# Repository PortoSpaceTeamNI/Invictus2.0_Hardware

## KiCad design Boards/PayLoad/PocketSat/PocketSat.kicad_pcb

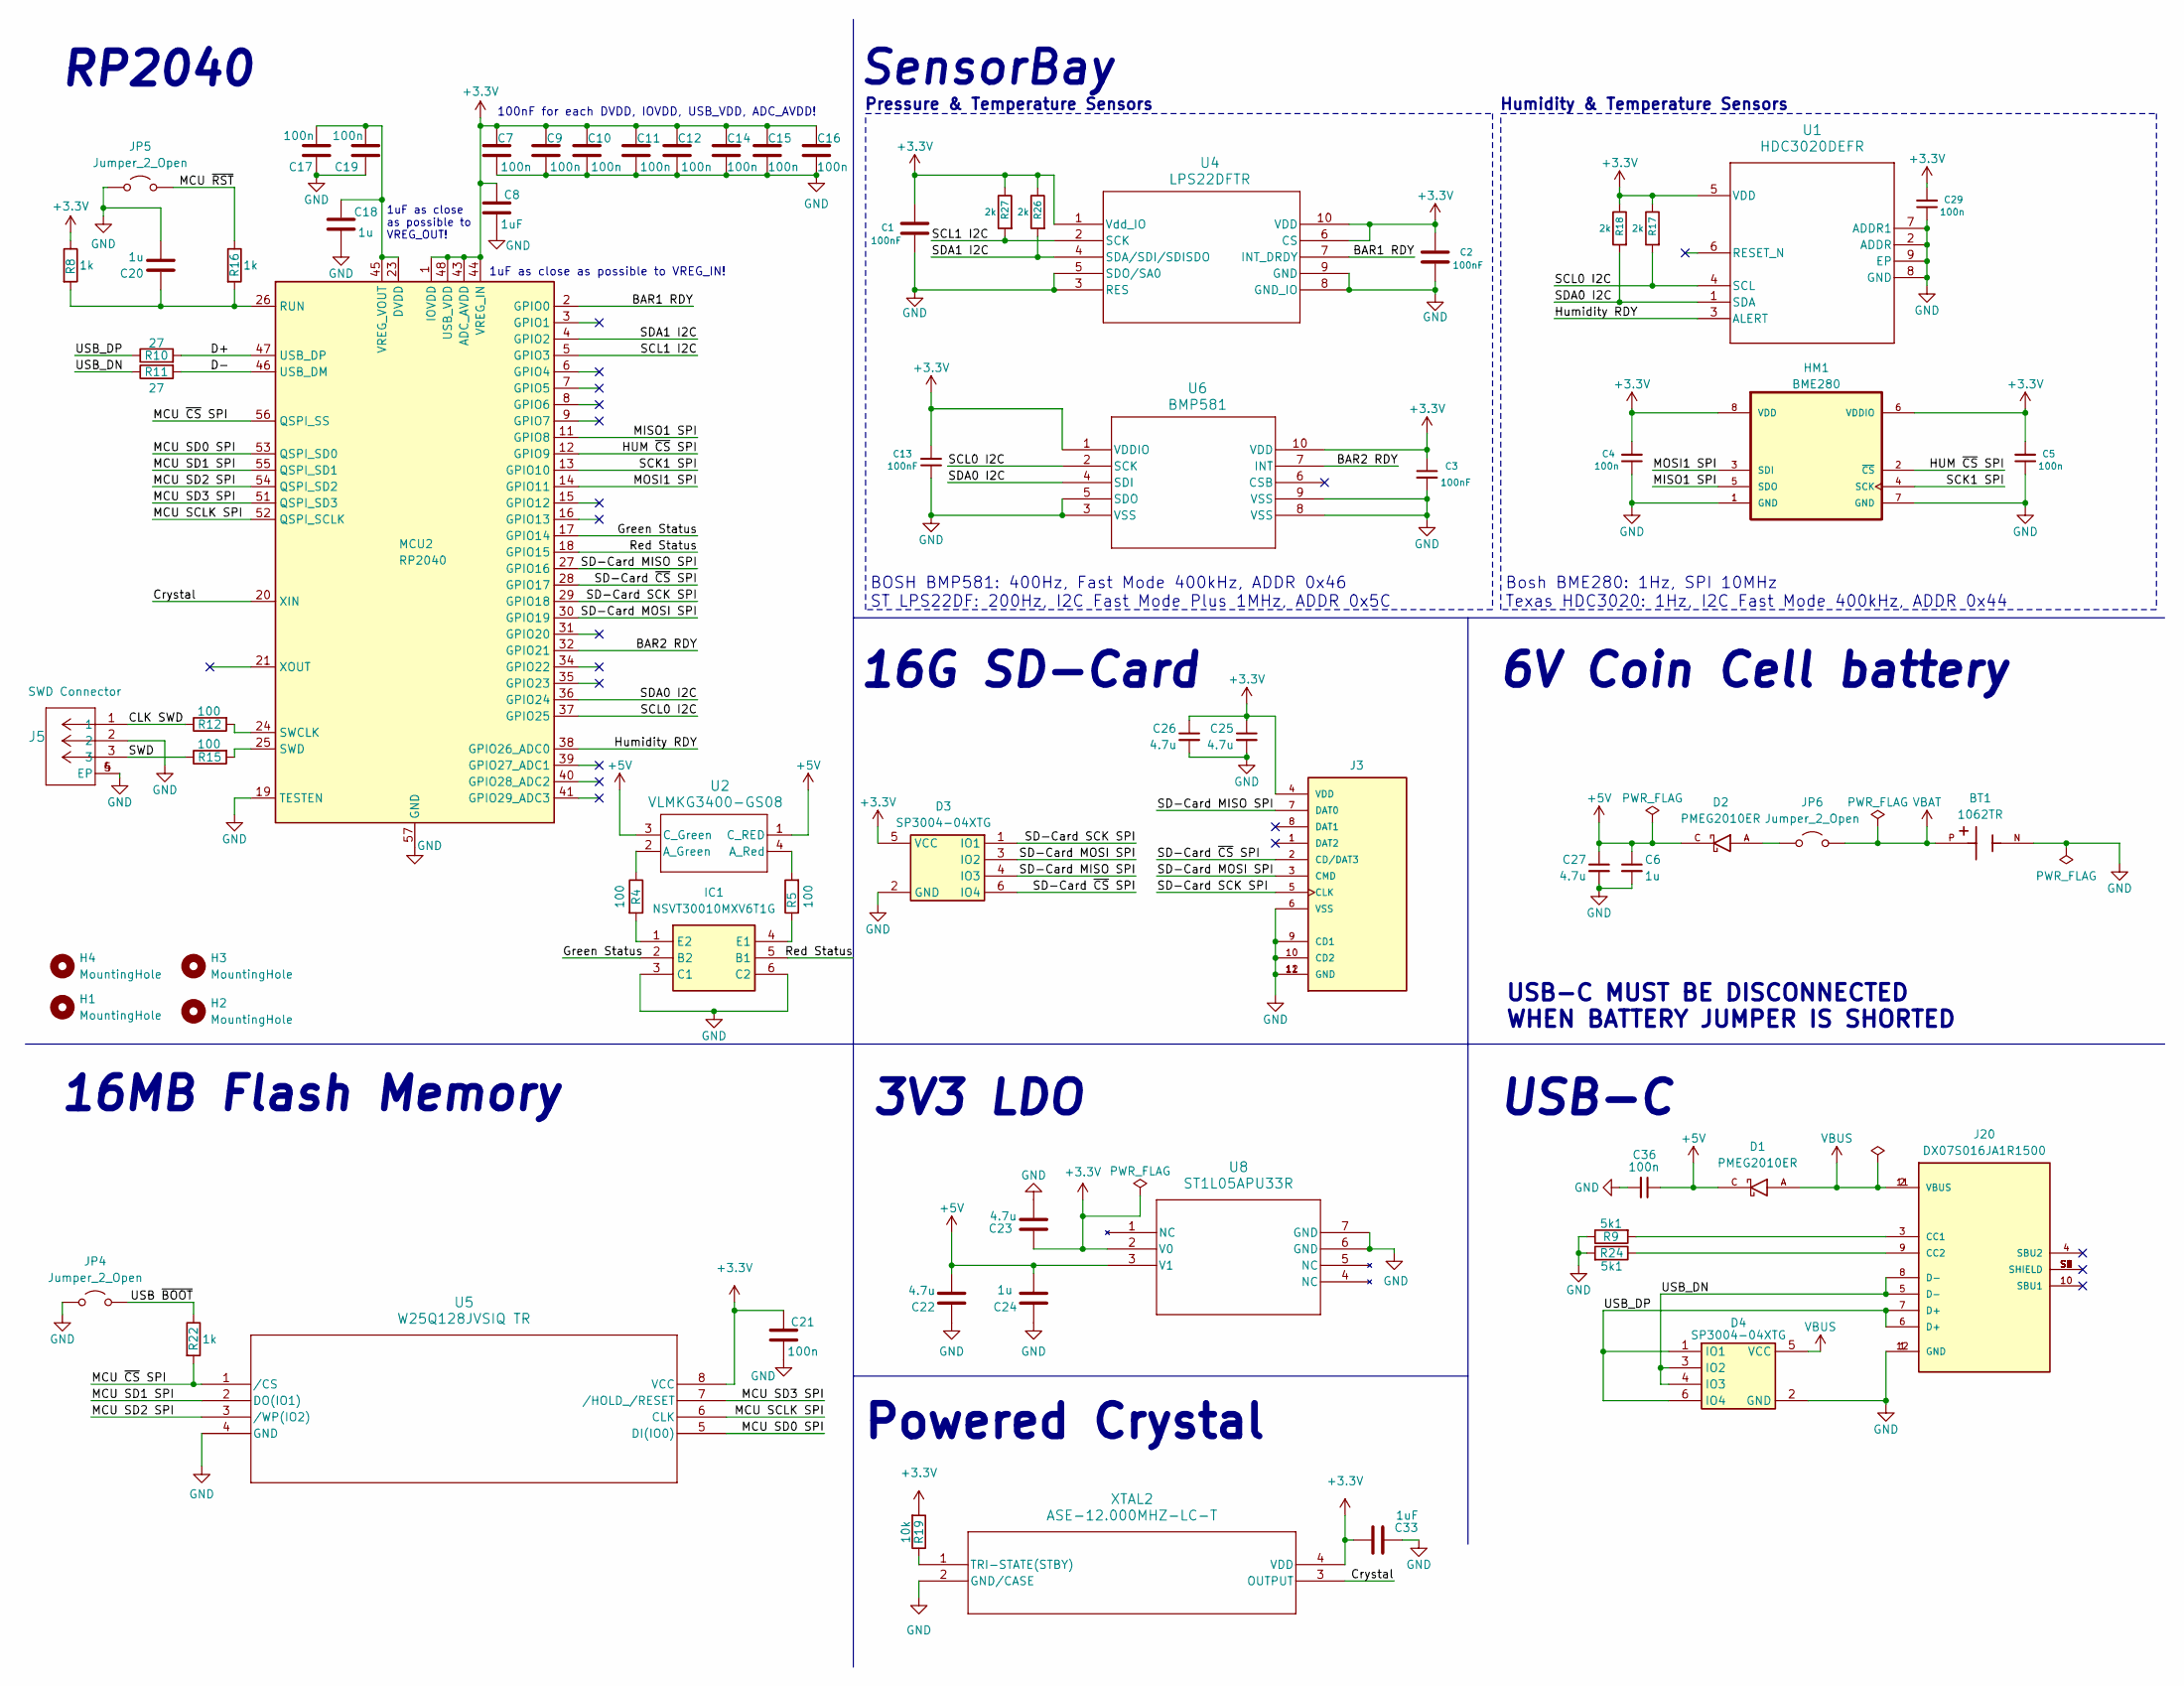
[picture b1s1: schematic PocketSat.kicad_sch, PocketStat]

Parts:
BT1: 1062TR; BAT_1062TR; PARTREV F
C1, C2, C3, C13: 100nF; Capacitor_0402
C4, C5, C7, C9, C10, C11, C12, C14, C15, C16, C17, C19, C21, C29, C36: 100n; Capacitor_0402
C6, C18, C20, C24: 1u; Capacitor_0402
C8, C33: 1uF; Capacitor_0402
C22, C23, C25, C26, C27: 4.7u; Capacitor_0402
D1, D2: PMEG2010ER; SODFL3517X110N; PARTREV 01
D3, D4: SP3004-04XTG; SOT563_LTF; Mouser Part Number 576-SP3004-04XTG
H1, H2, H3, H4: MountingHole; MountingHole_2.2mm_M2_ISO7380
HM1: BME280; Mouser Part Number 262-BME280
IC1: NSVT30010MXV6T1G; SOT-563_1P3X1P7_ONS; Mouser Part Number 863-NSVT30010MXV6T1G
J3: MEM2061-01-188-00-A_REVA; GCT_MEM2061-01-188-00-A_REVA
J5: BM03B-SRSS-TBLFSN; CONN_BM03B-SRSS-TBLFSN_JST
J20: DX07S016JA1R1500; JAE_DX07S016JA1R1500; PARTREV 1
JP4, JP5, JP6: Jumper_2_Open; SolderJumper-2_P1.3mm_Open_RoundedPad1.0x1.5mm
MCU2: RP2040; QFN56_7X7_RPI
R4, R5: 100; RES_0603
R8, R16, R22: 1k; RES_0402
R9, R24: 5k1; RES_0402
R10, R11: 27; RES_0402
R12, R15: 100; RES_0402
R17, R18, R26, R27: 2k; RES_0402
R19: 10k; RES_0402
U1: HDC3020DEFR; DEF0008A-IPC_C
U2: VLMKG3400-GS08; SMT_00-GS08_VIS
U4: LPS22DFTR; QFN_22DFTR_STM
U5: W25Q128JVSIQ TR; SOIC_208MIL_WIN
U6: BMP581; QFN10_BMP581_BOS
U8: ST1L05APU33R; DFN_5APU33R_STM
XTAL2: ASE-12.000MHZ-LC-T; ASE24576MHZLCT

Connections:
+3.3V: C1.2, C2.2, C3.1, C4.2, C5.2, C7.1, C8.1, C9.1, C10.1, C11.1, C12.1, C13.2, C14.1, C15.1, C16.1, C21.1, C23.2, C25.1, C26.1, C29.2, C33.1, D3.5 (VCC), HM1.6 (VDDIO), HM1.8 (VDD), J3.4 (VDD), MCU2.1 (IOVDD), MCU2.10 (IOVDD), MCU2.22 (IOVDD), MCU2.33 (IOVDD), MCU2.42 (IOVDD), MCU2.43 (ADC_AVDD), MCU2.44 (VREG_IN), MCU2.48 (USB_VDD), MCU2.49 (IOVDD), R8.1, R17.1, R18.1, R19.2, R26.1, R27.1, U1.5 (VDD), U4.1 (Vdd_IO), U4.6 (CS), U4.10 (VDD), U5.8 (VCC), U6.1 (VDDIO), U6.10 (VDD), U8.2 (V0), XTAL2.4 (VDD)
+5V: C6.1, C22.2, C24.2, C27.1, C36.1, D1.C, D2.C, U2.1 (C_RED), U2.3 (C_Green), U8.3 (V1)
/BAR1 RDY: MCU2.2 (GPIO0), U4.7 (INT_DRDY)
/BAR2 RDY: MCU2.32 (GPIO21), U6.7 (INT)
/CLK SWD: J5.1, R12.1
/Crystal: MCU2.20 (XIN), XTAL2.3 (OUTPUT)
/D+: MCU2.47 (USB_DP), R10.2
/D-: MCU2.46 (USB_DM), R11.2
/Green Status: IC1.2 (B2), MCU2.17 (GPIO14)
/HUM ~CS SPI: HM1.2 (~CS), MCU2.12 (GPIO9)
/Humidity RDY: MCU2.38 (GPIO26_ADC0), U1.3 (ALERT)
/MCU SCLK SPI: MCU2.52 (QSPI_SCLK), U5.6 (CLK)
/MCU SD0 SPI: MCU2.53 (QSPI_SD0), U5.5 (DI(IO0))
/MCU SD1 SPI: MCU2.55 (QSPI_SD1), U5.2 (DO(IO1))
/MCU SD2 SPI: MCU2.54 (QSPI_SD2), U5.3 (/WP(IO2))
/MCU SD3 SPI: MCU2.51 (QSPI_SD3), U5.7 (/HOLD_/RESET)
/MCU ~CS SPI: MCU2.56 (QSPI_SS), R22.2, U5.1 (/CS)
/MCU ~RST: JP5.2 (B), R16.1
/MISO1 SPI: HM1.5 (SDO), MCU2.11 (GPIO8)
/MOSI1 SPI: HM1.3 (SDI), MCU2.14 (GPIO11)
/Red Status: IC1.5 (B1), MCU2.18 (GPIO15)
/SCK1 SPI: HM1.4 (SCK), MCU2.13 (GPIO10)
/SCL0 I2C: MCU2.37 (GPIO25), R17.2, U1.4 (SCL), U6.2 (SCK)
/SCL1 I2C: MCU2.5 (GPIO3), R27.2, U4.2 (SCK)
/SD-Card ~CS SPI: D3.6 (IO4), J3.2 (CD/DAT3), MCU2.28 (GPIO17)
/SD-Card MISO SPI: D3.4 (IO3), J3.7 (DAT0), MCU2.27 (GPIO16)
/SD-Card MOSI SPI: D3.3 (IO2), J3.3 (CMD), MCU2.30 (GPIO19)
/SD-Card SCK SPI: D3.1 (IO1), J3.5 (CLK), MCU2.29 (GPIO18)
/SDA0 I2C: MCU2.36 (GPIO24), R18.2, U1.1 (SDA), U6.4 (SDI)
/SDA1 I2C: MCU2.4 (GPIO2), R26.2, U4.4 (SDA/SDI/SDISDO)
/SWD: J5.3, R15.1
/USB ~BOOT: JP4.2 (B), R22.1
/USB_DN: D4.3 (IO2), D4.4 (IO3), J20.5 (D-), J20.8 (D-), R11.1
/USB_DP: D4.1 (IO1), D4.6 (IO4), J20.6 (D+), J20.7 (D+), R10.1
GND: BT1.N, C1.1, C2.1, C3.2, C4.1, C5.1, C6.2, C7.2, C8.2, C9.2, C10.2, C11.2, C12.2, C13.1, C14.2, C15.2, C16.2, C17.1, C18.2, C19.1, C20.2, C21.2, C22.1, C23.1, C24.1, C25.2, C26.2, C27.2, C29.1, C33.2, C36.2, D3.2 (GND), D4.2 (GND), HM1.1 (GND), HM1.7 (GND), IC1.3 (C1), IC1.6 (C2), J3.6 (VSS), J3.9 (CD1), J3.10 (CD2), J3.11 (GND), J3.12 (GND), J5.2, J5.4 (EP), J5.5 (EP), J20.1 (GND), J20.12 (GND), JP4.1 (A), JP5.1 (A), MCU2.19 (TESTEN), MCU2.57 (GND), R9.1, R24.2, U1.2 (ADDR), U1.7 (ADDR1), U1.8 (GND), U1.9 (EP), U4.3 (RES), U4.5 (SDO/SA0), U4.8 (GND_IO), U4.9 (GND), U5.4 (GND), U6.3 (VSS), U6.5 (SDO), U6.8 (VSS), U6.9 (VSS), U8.6 (GND), U8.7 (GND), XTAL2.2 (GND/CASE)
unnamed: IC1.4 (E1), R5.1
unnamed: IC1.1 (E2), R4.2
unnamed: J20.3 (CC1), R9.2
unnamed: J20.9 (CC2), R24.1
unnamed: D2.A, JP6.1 (A)
unnamed: C20.1, MCU2.26 (RUN), R8.2, R16.2
unnamed: MCU2.24 (SWCLK), R12.2
unnamed: MCU2.25 (SWD), R15.2
unnamed: C17.2, C18.1, C19.2, MCU2.23 (DVDD), MCU2.45 (VREG_VOUT), MCU2.50 (DVDD)
unnamed: R4.1, U2.2 (A_Green)
unnamed: R5.2, U2.4 (A_Red)
unnamed: R19.1, XTAL2.1 (TRI-STATE(STBY))
VBAT: BT1.P, JP6.2 (B)
VBUS: D1.A, D4.5 (VCC), J20.2 (VBUS), J20.11 (VBUS)

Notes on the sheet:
BOSH BMP581: 400Hz, Fast Mode 400kHz, ADDR 0x46 ST LPS22DF: 200Hz, I2C Fast Mode Plus 1MHz, ADDR 0x5C
SensorBay
100nF for each DVDD, IOVDD, USB_VDD, ADC_AVDD!
3V3 LDO
RP2040
USB-C
Powered Crystal
Humidity & Temperature Sensors
16G SD-Card
6V Coin Cell battery
Pressure & Temperature Sensors
16MB Flash Memory
Bosh BME280: 1Hz, SPI 10MHz Texas HDC3020: 1Hz, I2C Fast Mode 400kHz, ADDR 0x44
1uF as close as possible to VREG_OUT!
1uF as close as possible to VREG_IN!
USB-C MUST BE DISCONNECTED WHEN BATTERY JUMPER IS SHORTED

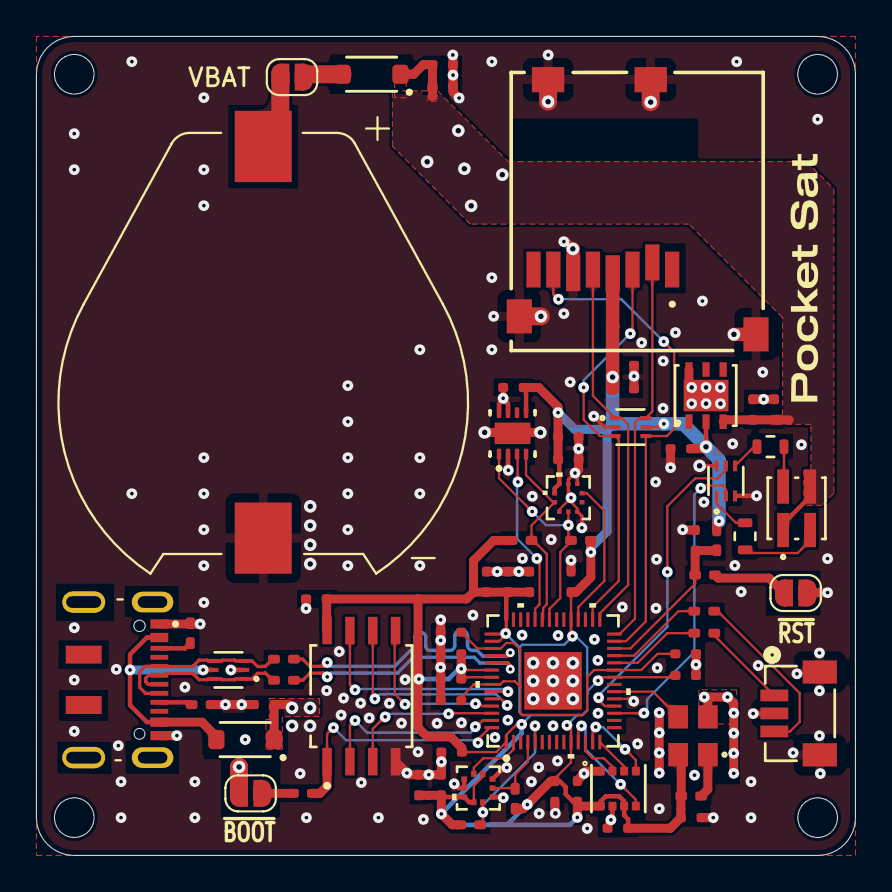
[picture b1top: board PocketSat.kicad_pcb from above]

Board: 4 copper layers, 45.5 x 45.5 mm, 71 parts (0 on the bottom side), 49 nets.

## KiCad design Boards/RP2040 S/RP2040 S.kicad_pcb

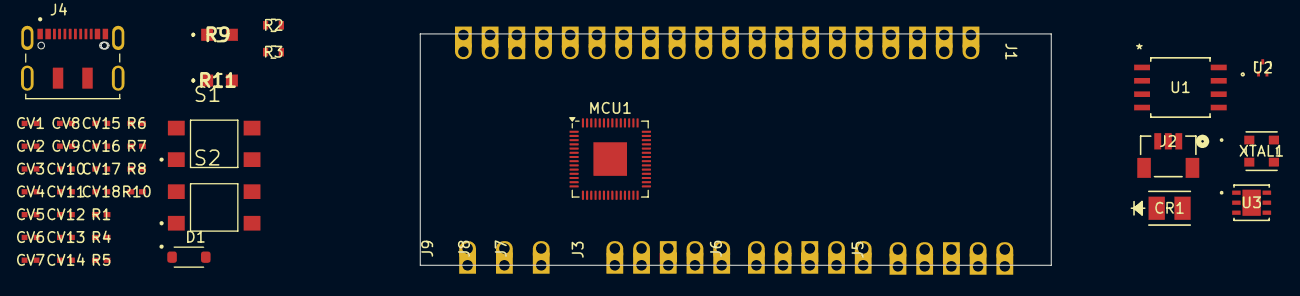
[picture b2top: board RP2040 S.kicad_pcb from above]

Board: 4 copper layers, 47 parts (0 on the bottom side), 57 nets, no tracks yet.

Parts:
CR1: VLMC3100-GS08; LED_PLCC_VSMB
CV1, CV3, CV6, CV13, CV17: 1uF; Capacitor_0402
CV2, CV4, CV5, CV7, CV8, CV9, CV10, CV11, CV12, CV14, CV18: 100nF; Capacitor_0402
CV15, CV16: 4.7uF; Capacitor_0402
D1: PMEG2010ER; SODFL3517X110N
J1: Conn_01x20_Socket; Pico_20pin
J2: BM03B-SRSS-TBLFSN; CONN_BM03B-SRSS-TBLFSN_JST
J3, J5, J6: Conn_01x05_Socket; Pico_05pin
J4: DX07S016JA1R1500; JAE_DX07S016JA1R1500
J7, J8, J9: Conn_01x01_Socket; Pico_01pin
MCU1: RP2040; QFN-56-1EP_7x7mm_P0.4mm_EP3.2x3.2mm
R1, R6, R10: 1k; RES_0402
R2, R3: 27; RES_0603
R4, R5: 100; RES_0402
R7: 10k; RES_0402
R8: 665; RES_0402
R9, R11: 5k1; RES_0805
S1, S2: TL3305CF160QG; SW_TL3305CF160QG
U1: W25Q128JVSIQ TR; SOIC_208MIL_WIN
U2: ESD7L5.0DT5G; SOT-723_0P85X1P25_ONS
U3: ST1L05APU33R; DFN_5APU33R_STM
XTAL1: ASE-12.000MHZ-LC-T; ASE-3.2X2.5_ABR

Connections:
+3.3V: CV5.1, CV6.1, CV7.1, CV8.1, CV9.1, CV10.1, CV11.1, CV12.1, CV13.1, CV14.1, CV16.2, CV18.1, MCU1.1 (IOVDD), MCU1.10 (IOVDD), MCU1.22 (IOVDD), MCU1.33 (IOVDD), MCU1.42 (IOVDD), MCU1.43 (ADC_AVDD), MCU1.44 (VREG_IN), MCU1.48 (USB_VDD), MCU1.49 (IOVDD), R1.1, R7.2, U1.8 (VCC), U3.2 (V0), XTAL1.4 (VDD)
/RP2040 Standard/+5V: CV15.2, CV17.2, D1.C, J3.1, U3.3 (V1)
/RP2040 Standard/GP0/UART0 TX: J1.20, MCU1.2 (GPIO0)
/RP2040 Standard/GP1/UART0 RX: J1.19, MCU1.3 (GPIO1)
/RP2040 Standard/GP2/UART0 CTS: J1.18, MCU1.4 (GPIO2)
/RP2040 Standard/GP3/UART0 RTS: J1.17, MCU1.5 (GPIO3)
/RP2040 Standard/GP4/UART1 TX: J1.15, MCU1.6 (GPIO4)
/RP2040 Standard/GP5/UART1 RX: J1.14, MCU1.7 (GPIO5)
/RP2040 Standard/GP6/UART1 CTS: J1.13, MCU1.8 (GPIO6)
/RP2040 Standard/GP7/UART1 RTS: J1.12, MCU1.9 (GPIO7)
/RP2040 Standard/GP8/SPI1 MISO: J1.10, MCU1.11 (GPIO8)
/RP2040 Standard/GP9/SPI1 ~CS: J1.9, MCU1.12 (GPIO9)
/RP2040 Standard/GP10/SPI1 SCK: J1.8, MCU1.13 (GPIO10)
/RP2040 Standard/GP11/SPI1 MOSI: J1.7, MCU1.14 (GPIO11)
/RP2040 Standard/GP12/I2C0 SDA: J1.5, MCU1.15 (GPIO12)
/RP2040 Standard/GP13/I2C0 SCL: J1.4, MCU1.16 (GPIO13)
/RP2040 Standard/GP14/I2C1 SDA: J1.2, MCU1.17 (GPIO14)
/RP2040 Standard/GP15/I2C1 SCL: J1.1, MCU1.18 (GPIO15)
/RP2040 Standard/GP16/SPI0 MISO: J3.2, MCU1.27 (GPIO16)
/RP2040 Standard/GP17/SPI0 ~CS: J3.3, MCU1.28 (GPIO17)
/RP2040 Standard/GP18/SPI0 SCK: J3.4, MCU1.29 (GPIO18)
/RP2040 Standard/GP19/SPI0 MOSI: J3.5, MCU1.30 (GPIO19)
/RP2040 Standard/GP20/PWM2 A/CLKIN 0: J5.2, MCU1.31 (GPIO20)
/RP2040 Standard/GP21/PWM2 B/CLKOUT 0: J5.3, MCU1.32 (GPIO21)
/RP2040 Standard/GP22/PWM3 A/CLKIN 1: J5.4, MCU1.34 (GPIO22)
/RP2040 Standard/GP23/PWM3 B/CLKOUT 1: J5.5, MCU1.35 (GPIO23)
/RP2040 Standard/GP24/PWM4 A: J6.2, MCU1.36 (GPIO24)
/RP2040 Standard/GP26_ADC0: J6.4, MCU1.38 (GPIO26_ADC0)
/RP2040 Standard/GP27_ADC1: J6.5, MCU1.39 (GPIO27_ADC1)
/RP2040 Standard/GP28_ADC2: J7.1, MCU1.40 (GPIO28_ADC2)
/RP2040 Standard/GP29_ADC3: J8.1, MCU1.41 (GPIO29_ADC3)
/RP2040 Standard/MCU QSPI_SCLK: MCU1.52 (QSPI_SCLK), U1.6 (CLK)
/RP2040 Standard/MCU QSPI_SD0: MCU1.53 (QSPI_SD0), U1.5 (DI(IO0))
/RP2040 Standard/MCU QSPI_SD1: MCU1.55 (QSPI_SD1), U1.2 (DO(IO1))
/RP2040 Standard/MCU QSPI_SD2: MCU1.54 (QSPI_SD2), U1.3 (/WP(IO2))
/RP2040 Standard/MCU QSPI_SD3: MCU1.51 (QSPI_SD3), U1.7 (/HOLD_/RESET)
/RP2040 Standard/MCU QSPI_SS: MCU1.56 (QSPI_SS), R10.2, U1.1 (/CS)
/RP2040 Standard/USB_DM: J4.5 (D-), J4.8 (D-), R3.1, U2.1
/RP2040 Standard/USB_DP: J4.6 (D+), J4.7 (D+), R2.1, U2.2
/RP2040 Standard/~RST: R6.1, S1.4
/RP2040 Standard/~USB_BOOT: R10.1, S2.4
CRYSTAL: MCU1.20 (XIN), XTAL1.3 (OUTPUT)
GND: CR1.1, CV1.2, CV2.1, CV3.2, CV4.1, CV5.2, CV6.2, CV7.2, CV8.2, CV9.2, CV10.2, CV11.2, CV12.2, CV13.2, CV14.2, CV15.1, CV16.1, CV17.1, CV18.2, J1.3, J1.6, J1.11, J1.16, J2.2, J4.1 (GND), J4.12 (GND), J5.1, J6.1, J6.3, J9.1, MCU1.19 (TESTEN), MCU1.57 (GND), R9.1, R11.1, S1.2, S2.2, U1.4 (GND), U2.3, U3.6 (GND), U3.7 (GND), XTAL1.2 (GND/CASE)
unnamed: CR1.2, R8.2
unnamed: D1.A, J4.2 (VBUS), J4.11 (VBUS)
unnamed: J2.1, R4.1
unnamed: J2.3, R5.1
unnamed: J4.3 (CC1), R11.2
unnamed: J4.9 (CC2), R9.2
unnamed: MCU1.37 (GPIO25), R8.1
unnamed: CV1.1, MCU1.26 (RUN), R1.2, R6.2
unnamed: MCU1.24 (SWCLK), R4.2
unnamed: MCU1.25 (SWD), R5.2
unnamed: MCU1.46 (USB_DM), R3.2
unnamed: MCU1.47 (USB_DP), R2.2
unnamed: CV2.2, CV3.1, CV4.2, MCU1.23 (DVDD), MCU1.45 (VREG_VOUT), MCU1.50 (DVDD)
unnamed: R7.1, XTAL1.1 (TRI-STATE(STBY))

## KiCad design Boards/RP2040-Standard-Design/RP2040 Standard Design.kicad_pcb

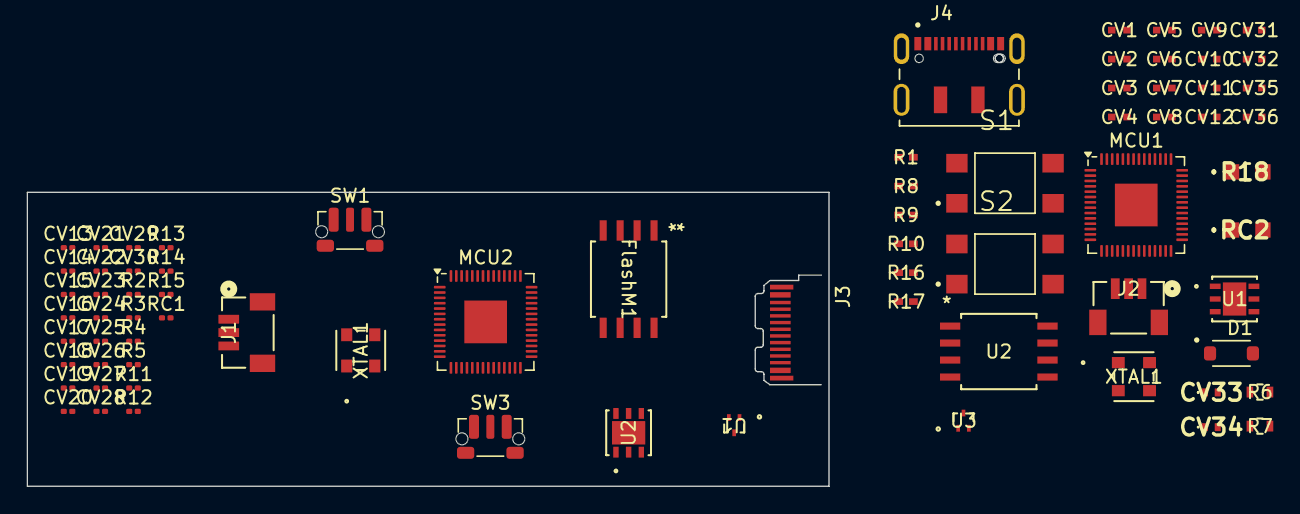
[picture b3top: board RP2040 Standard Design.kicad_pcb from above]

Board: 4 copper layers, 75 parts (0 on the bottom side), 47 nets, no tracks yet.

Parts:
CV1, CV3, CV6, CV31, CV35: 1uF; CAP_GCM155_MUR
CV2, CV4, CV5, CV7, CV8, CV9, CV10, CV11, CV12, CV32, CV36: 100nF; CAP_GCM155_MUR
CV13, CV15, CV18, CV25, CV29: 1uF; C_0201_0603Metric
CV14, CV16, CV17, CV19, CV20, CV21, CV22, CV23, CV24, CV26, CV30: 100nF; C_0201_0603Metric
CV27, CV28: 4.7uF; C_0201_0603Metric
CV33, CV34: 4.7uF; GRM15x
D1: PMEG2010ER; SODFL3517X110N
FlashM1: W25Q128JVSIQ_TR; SOIC_208MIL_WIN
J1, J2: BM03B-SRSS-TBLFSN; CONN_BM03B-SRSS-TBLFSN_JST
J3: USB_C; USB_C_Plug_JAE_DX07P024AJ1
J4: DX07S016JA1R1500; JAE_DX07S016JA1R1500
MCU1, MCU2: RP2040; QFN-56-1EP_7x7mm_P0.4mm_EP3.2x3.2mm
R1, R10, R17: 1k; RC0402N_VIS
R2, R12, R14: 1k; R_0201_0603Metric
R3, R4: 27; R_0201_0603Metric
R5, R11: 100; R_0201_0603Metric
R6, R7: 27; RES_R0603_ROM
R8, R9: 100; RC0402N_VIS
R13: 10k; R_0201_0603Metric
R15: 5k1; R_0201_0603Metric
R16: 10k; RC0402N_VIS
R18: 5k1; ERA6AEB101V
RC1: 5k1; R_0201_0603Metric
RC2: 5k1; ERA6AEB101V
S1, S2: TL3305CF160QG; SW_TL3305CF160QG
SW1, SW3: SW_Push; SW_Push_1P1T-MP_NO_Horizontal_Alps_SKRTLAE010
U1, U3: ESD7L5.0DT5G; SOT-723_0P85X1P25_ONS
U1#2, U2#2: ST1L05APU33R; DFN_5APU33R_STM
U2: W25Q128JVSIQ TR; SOIC_208MIL_WIN
XTAL1, XTAL1#2: ASE-12.000MHZ-LC-T; ASE-3.2X2.5_ABR

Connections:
+3.3V: CV5.1, CV6.1, CV7.1, CV8.1, CV9.1, CV10.1, CV11.1, CV12.1, CV17.1, CV18.1, CV19.1, CV20.1, CV21.1, CV22.1, CV23.1, CV24.1, CV25.1, CV26.1, CV28.2, CV30.1, CV31.1, CV32.1, CV34.2, CV36.1, FlashM1.8 (VCC), MCU1.1 (IOVDD), MCU1.10 (IOVDD), MCU1.22 (IOVDD), MCU1.33 (IOVDD), MCU1.42 (IOVDD), MCU1.43 (ADC_AVDD), MCU1.44 (VREG_IN), MCU1.48 (USB_VDD), MCU1.49 (IOVDD), MCU2.1 (IOVDD), MCU2.10 (IOVDD), MCU2.22 (IOVDD), MCU2.33 (IOVDD), MCU2.42 (IOVDD), MCU2.43 (ADC_AVDD), MCU2.44 (VREG_IN), MCU2.48 (USB_VDD), MCU2.49 (IOVDD), R1.1, R2.1, R13.2, R16.2, U1#2.2 (V0), U2.8 (VCC), U2#2.2 (V0), XTAL1.4 (VDD), XTAL1#2.4 (VDD)
/+5V: CV27.2, CV29.2, J3.A4 (VBUS), J3.A9 (VBUS), J3.B4 (VBUS), J3.B9 (VBUS), U2#2.3 (V1)
/MCU QSPI_SCLK: FlashM1.6 (CLK), MCU2.52 (QSPI_SCLK)
/MCU QSPI_SD0: FlashM1.5 (DI(IO0)), MCU2.53 (QSPI_SD0)
/MCU QSPI_SD1: FlashM1.2 (DO(IO1)), MCU2.55 (QSPI_SD1)
/MCU QSPI_SD2: FlashM1.3 (/WP(IO2)), MCU2.54 (QSPI_SD2)
/MCU QSPI_SD3: FlashM1.7 (/HOLD_/RESET), MCU2.51 (QSPI_SD3)
/MCU QSPI_SS: FlashM1.1 (/CS), MCU2.56 (QSPI_SS), R14.2
/RP2040 Standard/+5V: CV33.2, CV35.2, D1.C, U1#2.3 (V1)
/RP2040 Standard/MCU QSPI_SCLK: MCU1.52 (QSPI_SCLK), U2.6 (CLK)
/RP2040 Standard/MCU QSPI_SD0: MCU1.53 (QSPI_SD0), U2.5 (DI(IO0))
/RP2040 Standard/MCU QSPI_SD1: MCU1.55 (QSPI_SD1), U2.2 (DO(IO1))
/RP2040 Standard/MCU QSPI_SD2: MCU1.54 (QSPI_SD2), U2.3 (/WP(IO2))
/RP2040 Standard/MCU QSPI_SD3: MCU1.51 (QSPI_SD3), U2.7 (/HOLD_/RESET)
/RP2040 Standard/MCU QSPI_SS: MCU1.56 (QSPI_SS), R17.2, U2.1 (/CS)
/RP2040 Standard/USB_DM: J4.5 (D-), J4.8 (D-), R7.1, U3.1
/RP2040 Standard/USB_DP: J4.6 (D+), J4.7 (D+), R6.1, U3.2
/RP2040 Standard/~RST: R10.1, S2.4
/RP2040 Standard/~USB_BOOT: R17.1, S1.4
/USB_DM: J3.A7 (D-), J3.B7 (D-), R4.1, U1.1
/USB_DP: J3.A6 (D+), J3.B6 (D+), R3.1, U1.2
/~RST: R12.1, SW1.2
/~USB_BOOT: R14.1, SW3.2
CRYSTAL: MCU1.20 (XIN), MCU2.20 (XIN), XTAL1.3 (OUTPUT), XTAL1#2.3 (OUTPUT)
GND: CV1.2, CV2.1, CV3.2, CV4.1, CV5.2, CV6.2, CV7.2, CV8.2, CV9.2, CV10.2, CV11.2, CV12.2, CV13.2, CV14.1, CV15.2, CV16.1, CV17.2, CV18.2, CV19.2, CV20.2, CV21.2, CV22.2, CV23.2, CV24.2, CV25.2, CV26.2, CV27.1, CV28.1, CV29.1, CV30.2, CV31.2, CV32.2, CV33.1, CV34.1, CV35.1, CV36.2, FlashM1.4 (GND), J1.2, J2.2, J3.A1 (GND), J3.A12 (GND), J3.B1 (GND), J3.B12 (GND), J4.1 (GND), J4.12 (GND), MCU1.19 (TESTEN), MCU1.57 (GND), MCU2.19 (TESTEN), MCU2.57 (GND), R15.1, R18.1, RC1.1, RC2.1, S1.2, S2.2, SW1.1, SW3.1, U1.3, U1#2.6 (GND), U1#2.7 (GND), U2.4 (GND), U2#2.6 (GND), U2#2.7 (GND), U3.3, XTAL1.2 (GND/CASE), XTAL1#2.2 (GND/CASE)
unnamed: D1.A, J4.2 (VBUS), J4.11 (VBUS)
unnamed: J1.1, R5.1
unnamed: J1.3, R11.1
unnamed: J2.1, R9.1
unnamed: J2.3, R8.1
unnamed: J3.A5 (CC1), R15.2
unnamed: J3.B5 (CC2), RC1.2
unnamed: J4.3 (CC1), RC2.2
unnamed: J4.9 (CC2), R18.2
unnamed: CV1.1, MCU1.26 (RUN), R1.2, R10.2
unnamed: MCU1.24 (SWCLK), R8.2
unnamed: MCU1.25 (SWD), R9.2
unnamed: MCU1.46 (USB_DM), R7.2
unnamed: MCU1.47 (USB_DP), R6.2
unnamed: CV2.2, CV3.1, CV4.2, MCU1.23 (DVDD), MCU1.45 (VREG_VOUT), MCU1.50 (DVDD)
unnamed: CV13.1, MCU2.26 (RUN), R2.2, R12.2
unnamed: MCU2.24 (SWCLK), R5.2
unnamed: MCU2.25 (SWD), R11.2
unnamed: MCU2.46 (USB_DM), R4.2
unnamed: MCU2.47 (USB_DP), R3.2
unnamed: CV14.2, CV15.1, CV16.2, MCU2.23 (DVDD), MCU2.45 (VREG_VOUT), MCU2.50 (DVDD)
unnamed: R13.1, R16.1, XTAL1.1 (TRI-STATE(STBY)), XTAL1#2.1 (TRI-STATE(STBY))

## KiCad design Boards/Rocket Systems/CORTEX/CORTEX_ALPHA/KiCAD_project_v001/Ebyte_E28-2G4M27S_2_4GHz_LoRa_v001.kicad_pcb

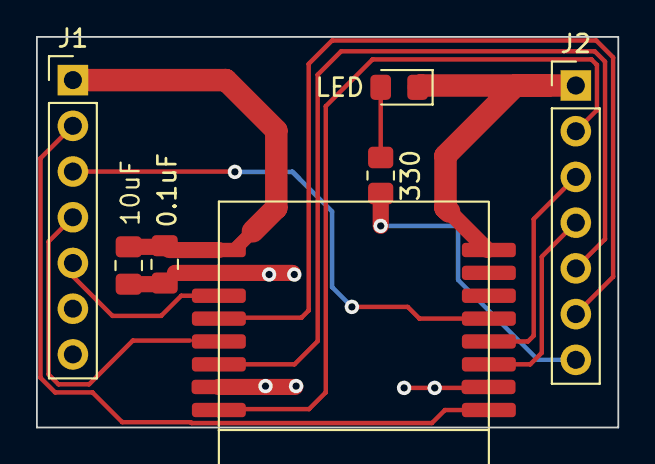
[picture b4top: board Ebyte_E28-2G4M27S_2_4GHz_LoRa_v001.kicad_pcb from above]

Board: 2 copper layers, 32.3 x 21.7 mm, 7 parts (0 on the bottom side), 13 nets.

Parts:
C1: 0.1uF; C_0805_2012Metric_Pad1.18x1.45mm_HandSolder
C2: 10uF; C_0805_2012Metric_Pad1.18x1.45mm_HandSolder
D1: LED; LED_0805_2012Metric_Pad1.15x1.40mm_HandSolder
J1, J2: Conn_01x07_Male; PinHeader_1x07_P2.54mm_Vertical
R1: 330; R_0805_2012Metric_Pad1.20x1.40mm_HandSolder
U1: E28-2G4M27S_LoRa; E28-2G4M27S

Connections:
D3: J1.3, U1.13 (DI01)
D4: J1.2, U1.9 (TX_EN)
D5: J2.2, U1.8 (RX_EN)
D6: J2.7, R1.1
D7: J2.3, U1.12 (BUSY)
D9: J2.4, U1.11 (NRESET)
D10/SS: J2.5, U1.6 (NSS_CTS)
D11/MOSI: J2.6, U1.4 (MOSI_RX)
D12/MISO: J1.5, U1.3 (MISO_TX)
D13/SCK: J1.4, U1.5 (SCK_RTS)
GND: C1.2, C2.2, D1.1 (K), J2.1, U1.2 (GND), U1.7 (GND), U1.10 (GND), U1.16 (GND)
unnamed: D1.2 (A), R1.2
VCC: C1.1, C2.1, J1.1, U1.1 (3.3V)
